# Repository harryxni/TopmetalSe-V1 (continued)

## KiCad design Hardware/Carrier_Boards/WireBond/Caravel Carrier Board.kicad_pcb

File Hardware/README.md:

# Hardware 
This directory contains the design files for using and testing the TopmetalSe.

## Test PCB, the UW Caravel Test Board
This board is the primary board used for testing as it contains all of the electronics necessary for running the chip.

A large part of this board is concerned with running the [caravel SOC](https://caravel-harness.readthedocs.io/en/latest/index.html), which is a part of the chip that we ultimatly do not use much. However, it is important to know that we can communicate with it, if necessary. It can also be useful to test I/O connections and make sure the chip is powered on/works as expected. As a result, much of this board is copied over from the [efabless caravel boards](https://github.com/efabless/caravel_board). A lot of the communication with the caravel SOC is done over USB via the FTDI chip and requires the clock to be on. For actual chip testing, please solder a jumper over J4 to turn the clock off to reduce the electronic noise.

The other part of the board is concerned with running the TopmetalSe, which happens in three categories: biasing, clocking and readout. 

The biasing of the chip is handled via the [Texas Instruments DAC 8568](https://www.ti.com/product/DAC8568?utm_source=google&utm_medium=cpc&utm_campaign=asc-null-null-GPN_EN-cpc-pf-google-wwe&utm_content=DAC8568&ds_k=DAC8568&DCM=yes&gclid=EAIaIQobChMIwIbj3O62_wIV-y-tBh3P_wriEAAYASAAEgLwtPD_BwE&gclsrc=aw.ds), which is an 8 Channel Digital to Analog Conveter. That is, we send digital commands and it outputs an analog voltage. The digital communication part is handled by an external FPGA, and the commands are generated via [software bit banging](https://github.com/selena0vbb/TopmetalSe_Sequencer/blob/main/util/DAC_control.py). These analog voltages are used as a bias either to source/sink a current or as a voltage bias on a transistor gate. 

The clocking of the chip is entirely handled by the external FPGAa and its firmware, so please look elsewhere for that. In the PCB design files, there are level shifters on the clocking signals to shift from the FPGA 3.3V signals to what I had assumed to be the caravel's 1.8V logic levels. However, the caravel harness actually expects 3.3V signals, so these level shifters are not soldered on and a jumper wire is used to make these connections.

There are two output signals coming from the TopmetalSe, an output for the large array (LA) and an output for the small array (SA). Both of these signals are readout using an opamp on the PCB. 

## Carrier Boards
To connect to the chip, we use a collection of adapter boards. This allows us to hotswap in any chip we want for testing. Now, the topmetalSe comes in a variety of packages, each of which has its own unique carrier board to accomdate the package. The carrier board is then plugged into the test board via 50 mil pins.

__One design fault is that the carriers can easily be plugged in incorrectly, causing undesired shorts. Please double check the pins and lined up correctly and in the correct orientation, as the header pins are symmetric. This applies to all carrier boards but the M.2 adapter.__

### M.2 Adapter Board
EFabless provided us with many QFN packaged chips. QFN, or quad flat no-leads, is an industry standard package for chips. Inside, chips are wire bonded to the frame and then encapsulated in plastic. This means that the QFN packages provide us with all the electrical capabilities, but none of the charge-sensing aspects of our device. __Please use these QFN packages to test and play around with learning to run the circuit__. Because we have so many and everything is encapsulated, there is very little chance of damaging these devices.

The QFN packages are/can be soldered onto a M.2 breakout board. EFabless provides the (design files)[https://github.com/efabless/caravel_board/tree/main/hardware/breakout/caravel-M.2-card-QFN] for these, so please look there if you need to. If you need more, the QFN packages must be soldered onto more M.2 breakouts.

The M.2 breakout boards can be attached to our test board via the M.2 adapter board.

### Wire Bonded

For charge-sensing, we must use the bare dies. The wire bonded carrier boards are pretty simple, as the bond pads go in the same order as the bond pads on the chip. The one key is that __the wire bonded board must be ENEPIG coated (not ENIG)__. If you order more, please make sure of this.

### Flip Chip

### aSe Flip Chip

## FPGA
For the FPGA, we use an external [BASYS3 Board](https://digilent.com/shop/basys-3-artix-7-fpga-trainer-board-recommended-for-introductory-users/). It is connected to the test board via PMOD connectors. Now, there is a mistake in the PCB design where the PMOD headers are actually flipped, so you must be careful to flip the PMOD connectors. Please see the PCB layout for this as well as the labels on the PCB to make sure things are aligned (ie Pin 1 to Pin 1). The firmware for the FPGA is discussed elsewhere.

## Sapphire Interposer
In flip chip packages, the chip is bonded to a flat piece known as the interposer. It is made with a 200/300 um thick piece of sapphire, which has conductive traces patterned and deposited onto it (usually O(100) nm of Al and Au). The side with traces on it is the bottom side. The top side is used for aSe Deposition and contains a conductive mesh. There is also a window opening where the pixel array is, which we typically laser cut.

## Electronic Equipment

## Mechanical Parts

## TopmetalSe Design Files
The majority of the design files for the TopmetalSe-V1 are contained in a [separate repo](https://github.com/harryxni/TopMetalSe-OpenMPW6). I include some general files in this repo as a reference.

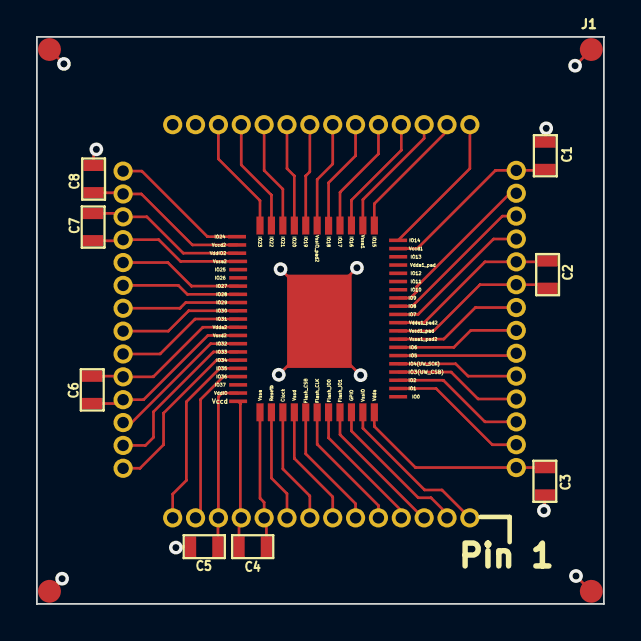
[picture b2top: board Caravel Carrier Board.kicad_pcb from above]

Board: 4 copper layers, 31.5 x 31.5 mm, 13 parts (0 on the bottom side), 46 nets.

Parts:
C1, C2, C3, C4, C5, C6, C7, C8: 0.1uF; SM0603
J1, J2, J3, J4: Shield_Pad; .050_Pad_TP
U1: Caravel_Carrier

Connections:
/Vccd: C4.1, U1.11 (Vccd), U1.Vccd
/Vccd1: C1.1, U1.43 (Vccd1), U1.Vccd1
/Vccd2: C8.1, U1.27 (Vccd2), U1.Vccd2
/VddIO: C5.1, U1.12 (VddIO), U1.VddIO
/VddIO_2: C7.1, U1.26 (VddIO_2), U1.VddIO_2
/Vdda: C3.1, U1.56 (Vdda), U1.Vdda
/Vdda1: C2.1, U1.47 (Vdda1_pad2), U1.Vdda1_pad2
/Vdda2: C6.1, U1.19 (Vdda2), U1.Vdda2
GND: C1.2, C2.2, C3.2, C4.2, C5.2, C6.2, C7.2, C8.2, J1.1, J2.1, J3.1, J4.1, U1.1 (VssIO), U1.7 (Vssd), U1.10 (Vssa), U1.18 (Vssd2), U1.25 (Vssa2), U1.36 (VssIO_pad2), U1.40 (Vssa1), U1.48 (Vssd1_pad), U1.49 (Vssa1_pad2), U1.GND (Substrate_GND), U1.VssIO, U1.VssIO_pad2, U1.Vssa, U1.Vssa1, U1.Vssa1_pad2, U1.Vssa2, U1.Vssd, U1.Vssd1_pad, U1.Vssd2
unnamed: U1.8 (Clock(Caravel_SCK)), U1.Clock (Clock(Caravel_SCK))
unnamed: U1.5 (Flash_CLK), U1.Flash_CLK
unnamed: U1.6 (Flash_CSB(Caravel_CSB)), U1.Flash_CSB (Flash_CSB(Caravel_CSB))
unnamed: U1.4 (Flash_IO0(Caravel_D0)), U1.Flash_IO0 (Flash_IO0(Caravel_D0))
unnamed: U1.3 (Flash_IO1(Caravel_D1)), U1.Flash_IO1 (Flash_IO1(Caravel_D1))
unnamed: U1.2 (GPIO), U1.GPIO
unnamed: U1.55 (IO1(mprj_io[1]_SDO)), U1.IO1 (IO1(mprj_io[1]_SDO))
unnamed: U1.54 (IO2(mprj_io[2]_SDI)), U1.IO2 (IO2(mprj_io[2]_SDI))
unnamed: U1.53 (IO3(mprj_io[3]_CSB)), U1.IO3 (IO3(mprj_io[3]_CSB))
unnamed: U1.52 (IO4(mprj_io[4]_SCK)), U1.IO4 (IO4(mprj_io[4]_SCK))
unnamed: U1.51 (IO5(mprj_io[5]_ser_rx)), U1.IO5 (IO5(mprj_io[5]_ser_rx))
unnamed: U1.50 (IO6(LA_row_clk__ser_tx)), U1.IO6 (IO6(LA_row_clk__ser_tx))
unnamed: U1.46 (IO7(LA_row_ena)), U1.IO7 (IO7(LA_row_ena))
unnamed: U1.45 (IO8(LA_row_rst)), U1.IO8 (IO8(LA_row_rst))
unnamed: U1.44 (IO9(LA_row_data_in)), U1.IO9 (IO9(LA_row_data_in))
unnamed: U1.42 (IO14(LA_output)), U1.IO14 (IO14(LA_output))
unnamed: U1.41 (IO15(SA_output)), U1.IO15 (IO15(SA_output))
unnamed: U1.39 (IO16(AMP_IB)), U1.IO16 (IO16(AMP_IB))
unnamed: U1.38 (IO17(OUT_IB)), U1.IO17 (IO17(OUT_IB))
unnamed: U1.37 (IO18(NB2)), U1.IO18 (IO18(NB2))
unnamed: U1.35 (IO19(NB1)), U1.IO19 (IO19(NB1))
unnamed: U1.34 (IO20(SF_IB)), U1.IO20 (IO20(SF_IB))
unnamed: U1.33 (IO21(VBIAS)), U1.IO21 (IO21(VBIAS))
unnamed: U1.32 (IO22(VREF)), U1.IO22 (IO22(VREF))
unnamed: U1.31 (IO23(CSA_VREF)), U1.IO23 (IO23(CSA_VREF))
unnamed: U1.28 (IO24(Gring)), U1.IO24 (IO24(Gring))
unnamed: U1.24 (IO27(LA_col_clk)), U1.IO27 (IO27(LA_col_clk))
unnamed: U1.23 (IO28(LA_col_ena)), U1.IO28 (IO28(LA_col_ena))
unnamed: U1.22 (IO29(LA_col_rst)), U1.IO29 (IO29(LA_col_rst))
unnamed: U1.21 (IO30(LA__col_data_in)), U1.IO30 (IO30(LA__col_data_in))
unnamed: U1.20 (IO31(SA_row_sel2)), U1.IO31 (IO31(SA_row_sel2))
unnamed: U1.17 (IO32(SA_row_sel1)), U1.IO32 (IO32(SA_row_sel1))
unnamed: U1.16 (IO33(SA_row_sel0)), U1.IO33 (IO33(SA_row_sel0))
unnamed: U1.15 (IO34(SA_col_sel2)), U1.IO34 (IO34(SA_col_sel2))
unnamed: U1.14 (IO35(SA_col_sel1)), U1.IO35 (IO35(SA_col_sel1))
unnamed: U1.13 (IO36(SA_col_sel0)), U1.IO36 (IO36(SA_col_sel0))
unnamed: U1.9 (Resetb(~RST)), U1.Resetb (Resetb(~RST))

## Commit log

2024-08-02 Create README.md
    hardware folder
2024-08-02 Create README.MD
    firmware folder
2024-08-03 add some test board files
2024-08-05 added hardware files
2024-08-05 directory add
2024-08-10 started notebook
2024-08-10 added notebook;
2024-08-10 added analysis submodule
2024-10-22 adapter boards for vacuum feedthrough
2024-10-22 carrier board
2024-10-24 guard ring test notebook
2024-10-24 PE picture
